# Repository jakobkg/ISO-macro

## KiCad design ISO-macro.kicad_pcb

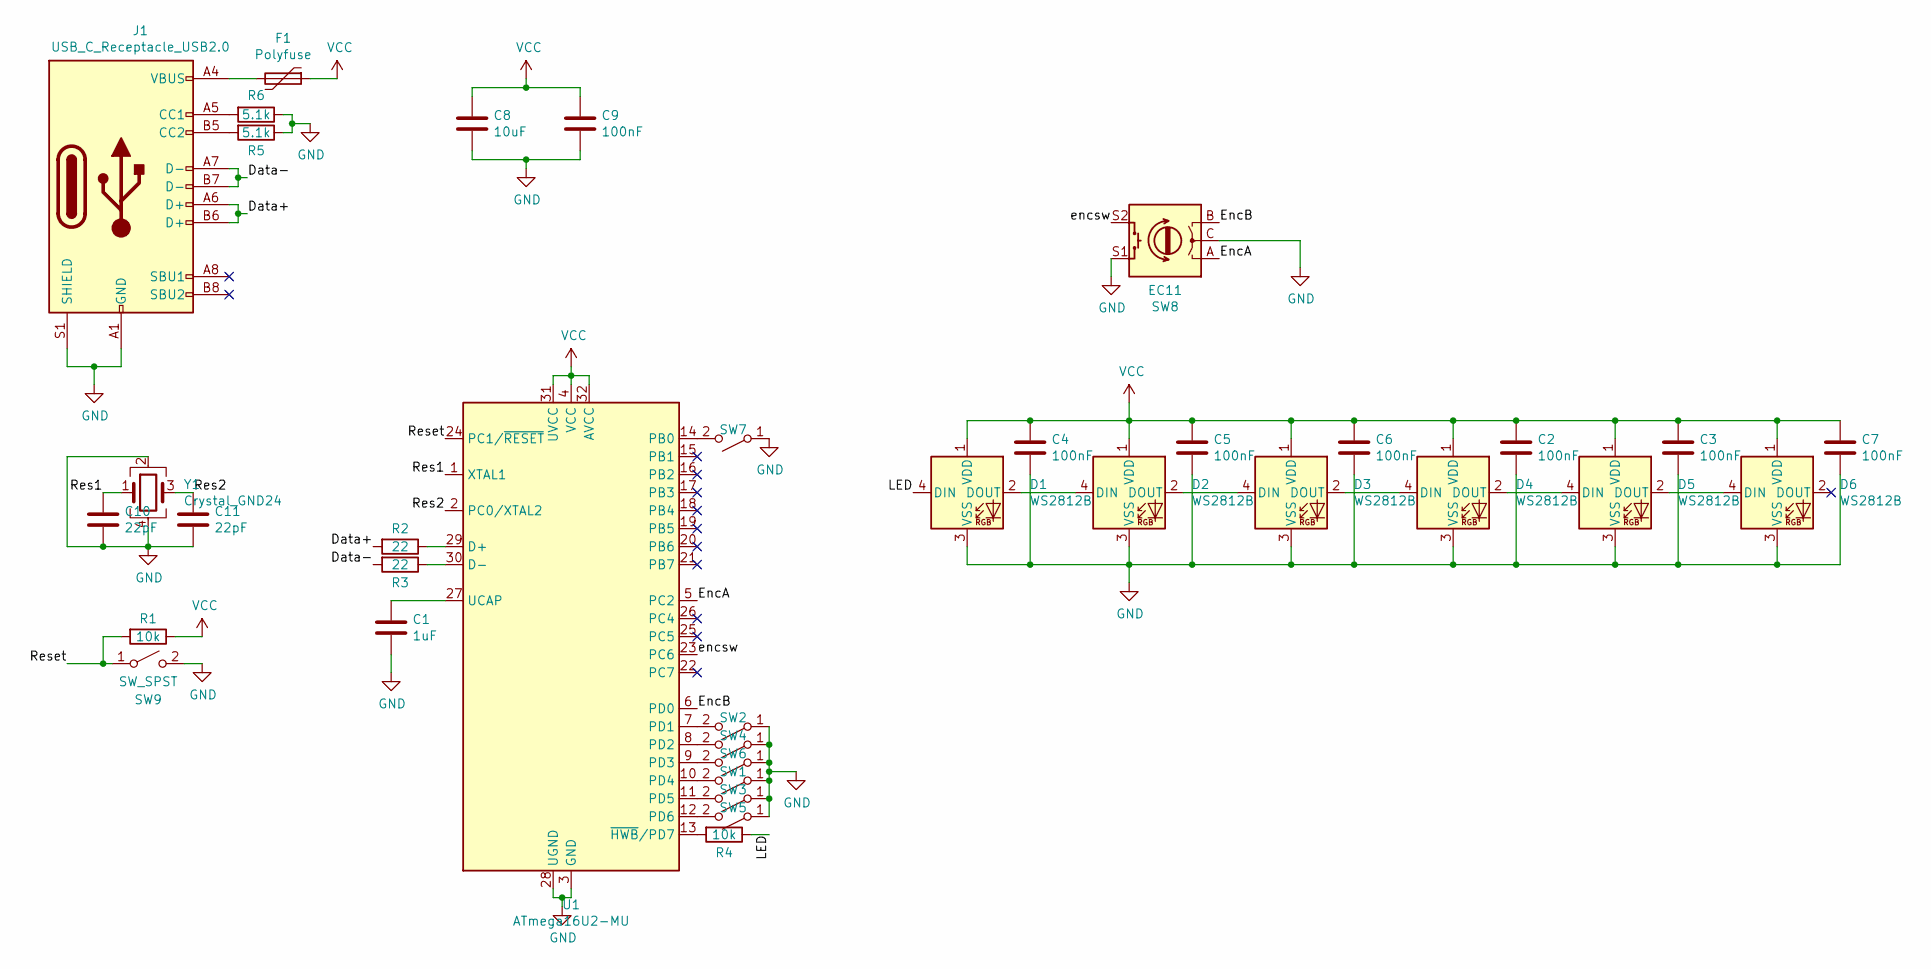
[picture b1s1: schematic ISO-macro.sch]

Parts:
C1: 1uF; C_0402_1005Metric; LCSC C52923
C2, C3, C4, C5, C6, C7, C9: 100nF; C_0402_1005Metric; LCSC C1525
C8: 10uF; C_0402_1005Metric; LCSC C15525
C10, C11: 22pF; C_0402_1005Metric; LCSC C183675
D1, D2, D3, D4, D5, D6: WS2812B; LED_SK6812MINI_PLCC4_3.5x3.5mm_P1.75mm; LCSC C527089
F1: Polyfuse; Fuse_1206_3216Metric; LCSC C70068
J1: USB_C_Receptacle_USB2.0; USB_C_Receptacle_HRO_TYPE-C-31-M-12; LCSC C167321
R1, R4: 10k; R_0402_1005Metric; LCSC C25744
R2, R3: 22; R_0402_1005Metric; LCSC C25092
R5, R6: 5.1k; R_0402_1005Metric; LCSC C25905
SW1: SW_SPST; SW_Cherry_MX_1.25u_PCB
SW2, SW3, SW4, SW5, SW6: SW_SPST; SW_Cherry_MX_1.00u_PCB
SW7: SW_SPST; SW_Cherry_MX_ISOEnter_PCB
SW8: EC11; RotaryEncoder_Alps_EC11E-Switch_Vertical_H20mm
SW9: SW_SPST; TestPoint_2Pads_Pitch2.54mm_Drill0.8mm
U1: ATmega16U2-MU; QFN-32-1EP_5x5mm_P0.5mm_EP3.1x3.1mm; LCSC C17317
Y1: Crystal_GND24; Crystal_SMD_3225-4Pin_3.2x2.5mm; LCSC C13738

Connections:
/Data+: J1.A6 (D+), J1.B6 (D+), R2.2
/Data-: J1.A7 (D-), J1.B7 (D-), R3.2
/EncA: SW8.A, U1.5 (PC2)
/EncB: SW8.B, U1.6 (PD0)
/LED: D1.4 (DIN), R4.1
/Res1: C10.1, U1.1 (XTAL1), Y1.1
/Res2: C11.1, U1.2 (PC0/XTAL2), Y1.3
/Reset: R1.2, SW9.1 (A), U1.24 (PC1/~RESET)
/encsw: SW8.S2, U1.23 (PC6)
GND: C1.2, C2.2, C3.2, C4.2, C5.2, C6.2, C7.2, C8.2, C9.2, C10.2, C11.2, D1.3 (VSS), D2.3 (VSS), D3.3 (VSS), D4.3 (VSS), D5.3 (VSS), D6.3 (VSS), J1.A1 (GND), J1.A12 (GND), J1.B1 (GND), J1.B12 (GND), J1.S1 (SHIELD), R5.1, R6.1, SW1.1 (A), SW2.1 (A), SW3.1 (A), SW4.1 (A), SW5.1 (A), SW6.1 (A), SW7.1 (A), SW8.C, SW8.S1, SW9.2 (B), U1.3 (GND), U1.28 (UGND), U1.33 (GND), Y1.2, Y1.4
unnamed: C1.1, U1.27 (UCAP)
unnamed: D1.2 (DOUT), D2.4 (DIN)
unnamed: D2.2 (DOUT), D3.4 (DIN)
unnamed: D3.2 (DOUT), D4.4 (DIN)
unnamed: D4.2 (DOUT), D5.4 (DIN)
unnamed: D5.2 (DOUT), D6.4 (DIN)
unnamed: F1.2, J1.A4 (VBUS), J1.A9 (VBUS), J1.B4 (VBUS), J1.B9 (VBUS)
unnamed: J1.A5 (CC1), R5.2
unnamed: J1.B5 (CC2), R6.2
unnamed: R2.1, U1.29 (D+)
unnamed: R3.1, U1.30 (D-)
unnamed: R4.2, U1.13 (~HWB~/PD7)
unnamed: SW1.2 (B), U1.10 (PD4)
unnamed: SW2.2 (B), U1.7 (PD1)
unnamed: SW3.2 (B), U1.11 (PD5)
unnamed: SW4.2 (B), U1.8 (PD2)
unnamed: SW5.2 (B), U1.12 (PD6)
unnamed: SW6.2 (B), U1.9 (PD3)
unnamed: SW7.2 (B), U1.14 (PB0)
VCC: C2.1, C3.1, C4.1, C5.1, C6.1, C7.1, C8.1, C9.1, D1.1 (VDD), D2.1 (VDD), D3.1 (VDD), D4.1 (VDD), D5.1 (VDD), D6.1 (VDD), F1.1, R1.1, U1.4 (VCC), U1.31 (UVCC), U1.32 (AVCC)

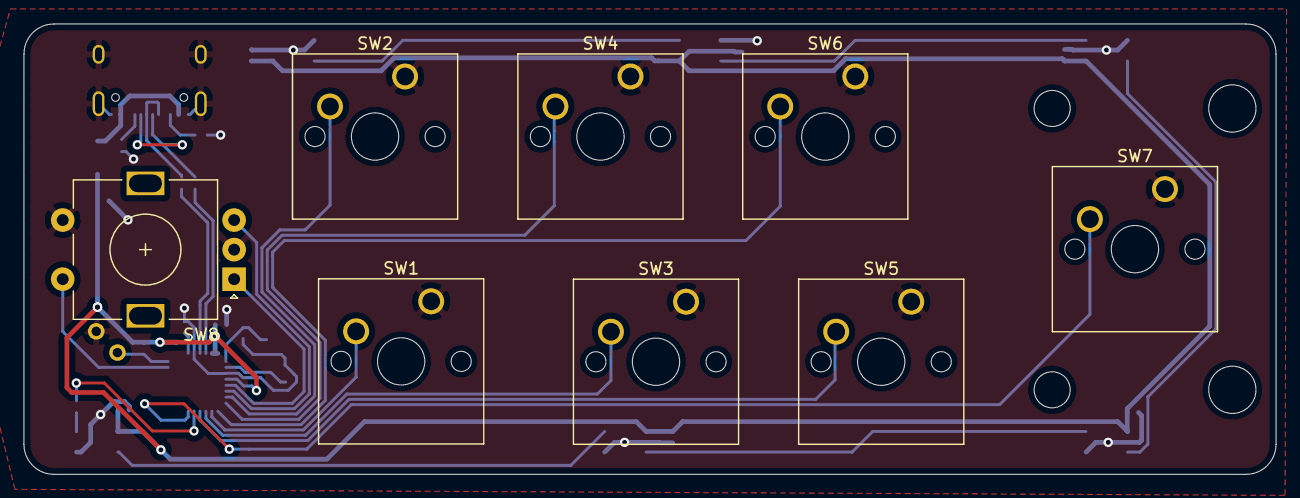
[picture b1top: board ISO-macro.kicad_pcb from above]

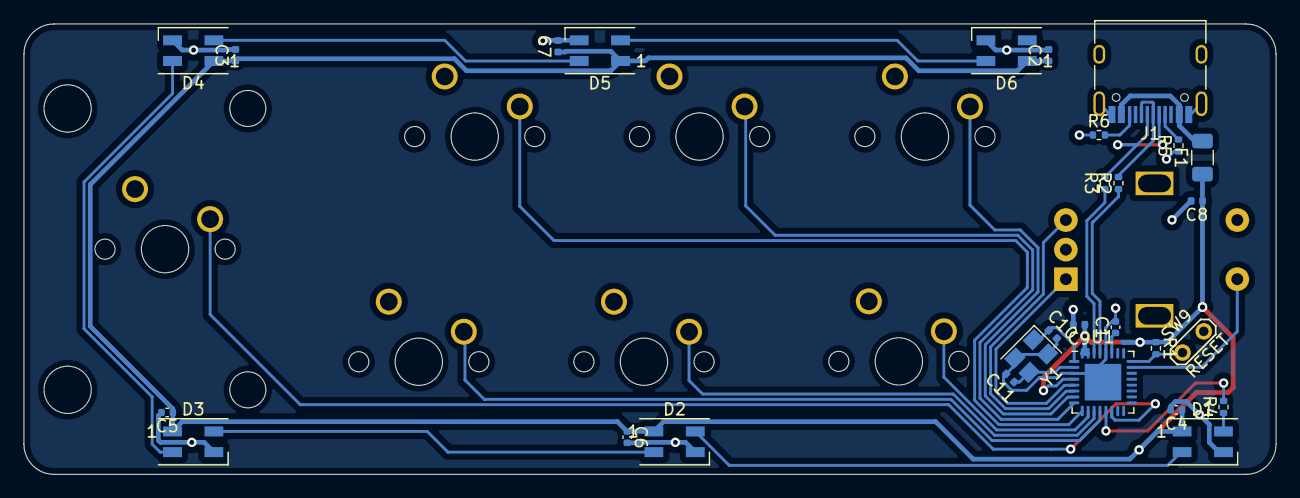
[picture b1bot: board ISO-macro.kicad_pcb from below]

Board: 2 copper layers, 105.9 x 38.1 mm, 36 parts (28 on the bottom side), 30 nets.

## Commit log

2021-06-05 add backlights, connect things
2021-06-05 update workflow and gitignore
2021-06-05 Rename ISO-macro.kiplot.yaml to ISO-macro.kibot.yaml
2021-06-05 updated MCU, removed filter for rot enc
    updated MCU, removed filter for rot enc
2021-06-05 reverted bugged schematic
2021-06-07 add bom list
2021-06-10 Add LEDs and power caps, routing
2021-06-10 rm unuseds
2021-06-10 Add NCs where appropriate
2021-06-10 Add power caps, LEDs, finish routing (#3)
    * wip
    * Add LEDs and power caps, routing
    * rm unuseds
    * Add NCs where appropriate
2021-06-16 update bom, change from integrated resonator to crystal
2021-06-16 add missing part number
2021-06-16 Change to basic, in-stock part numbers
2021-06-16 smaller reset footprint, move a few things
2021-06-25 firmware draft
2021-06-25 Via support
2021-06-25 underglow
2021-06-25 underglow (#5)
2021-07-01 RGB support in Via draft
